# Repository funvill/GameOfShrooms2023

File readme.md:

Working on [Idea 006 Procedurally Generated Glowing Mushroom Pcb](https://blog.abluestar.com/idea006-procedurally-generated-glowing-mushroom-pcb/) Using [p5js](https://p5js.org/) to generate the mushroom and [svg2shenzhen](https://github.com/badgeek/svg2shenzhen) to convert the SVG to KiCad.

For [Game of Shroom 2023](https://yumfactory.com/gameofshrooms/)

## Build

1. Open `p5js/index.html` in a browser
2. Right click and inspect the image, find the svg, copy the element, past the svg text into a new text document, save it as `output.svg`
3. Install [svg2shenzhen](https://github.com/badgeek/svg2shenzhen)
4. Open `output.svg` in inkscape.
5. Extention->svg2shenzhen->`1. Prep Document...`
6. Resize the image to fit within the page.
7. Copy red outline to the `edge.cuts` layer
8. Copy the black body to the `f.Cu` layer
9. Extention->svg2shenzhen->`2. Export to KiCad`

## Example

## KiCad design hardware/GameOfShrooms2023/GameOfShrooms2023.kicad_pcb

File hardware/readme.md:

Based on this design
https://github.com/adafruit/Adafruit-QT-Py-ESP32-S2-PCB/tree/main

## BOM

- CPU (C529594) ESP32-S2 https://jlcpcb.com/partdetail/EspressifSystems-ESP32S2/C529594
- LED (C2843785) WS2812B XL-5050RGBC-WS2812B https://jlcpcb.com/partdetail/Xinglight-XL_5050RGBCWS2812B/C2843785
- Antenna (C89334) https://jlcpcb.com/partdetail/JohansonDielectrics-2450AT18A100E/C89334
- Linear Voltage Regulators (LDO) (C51118) https://jlcpcb.com/partdetail/DiodesIncorporated-AP2112K_33TRG1/C51118

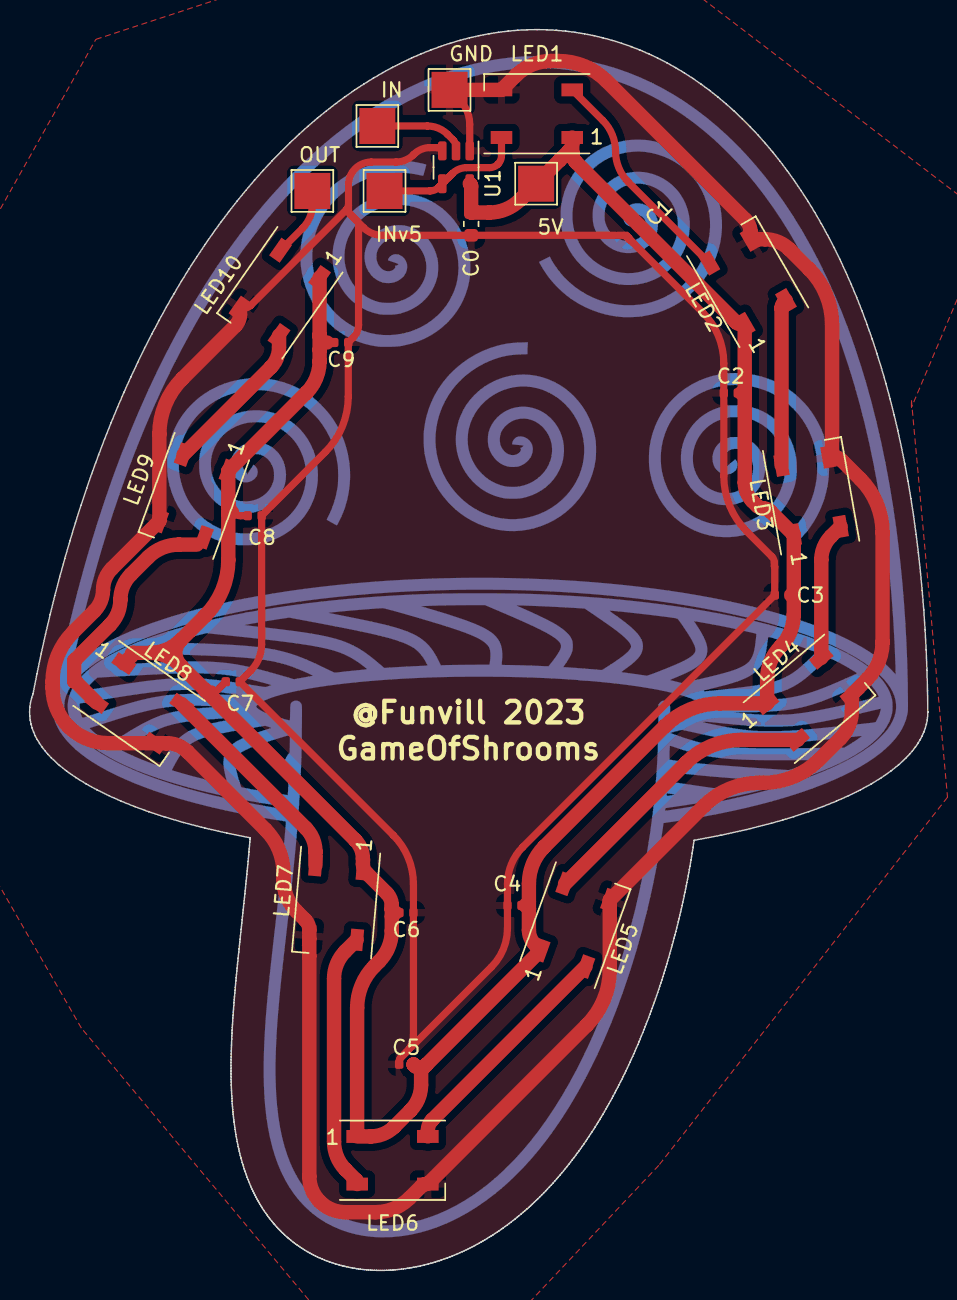
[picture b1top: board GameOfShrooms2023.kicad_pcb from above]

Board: 2 copper layers, 62.2 x 86.0 mm, 26 parts (0 on the bottom side), 14 nets.

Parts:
5V: TestPoint; TestPoint_Pad_2.5x2.5mm
C0: 10uF,10V,X5R; C_0603_1608Metric
C1, C2, C3, C4, C5, C6, C7, C8, C9: 1uF,25V,X5R; C_0402_1005Metric
GND: TestPoint; TestPoint_Pad_2.5x2.5mm
IN: TestPoint; TestPoint_Pad_2.5x2.5mm
INv5: TestPoint; TestPoint_Pad_2.5x2.5mm
LED1, LED2, LED3, LED4, LED5, LED6, LED7, LED8, LED9, LED10: WS2812B; LED_WS2812B_PLCC4_5.0x5.0mm_P3.2mm
OUT: TestPoint; TestPoint_Pad_2.5x2.5mm
U1: 74AHC1G125; SOT-23-5

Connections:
+5V: 5V.1, C0.1, C1.2, C2.2, C3.2, C4.2, C5.2, C6.2, C7.2, C8.2, C9.2, LED1.1 (VDD), LED2.1 (VDD), LED3.1 (VDD), LED4.1 (VDD), LED5.1 (VDD), LED6.1 (VDD), LED7.1 (VDD), LED8.1 (VDD), LED9.1 (VDD), LED10.1 (VDD), U1.5 (VCC)
GND: C0.2, C1.1, C2.1, C3.1, C4.1, C5.1, C6.1, C7.1, C8.1, C9.1, GND.1, LED1.3 (GND), LED2.3 (GND), LED3.3 (GND), LED4.3 (GND), LED5.3 (GND), LED6.3 (GND), LED7.3 (GND), LED8.3 (GND), LED9.3 (GND), LED10.3 (GND), U1.1, U1.3 (GND)
LED_IN: IN.1, U1.2
LED_OUT: LED10.2 (DOU), OUT.1
unnamed: INv5.1, LED1.4 (DIN), U1.4
unnamed: LED1.2 (DOU), LED2.4 (DIN)
unnamed: LED2.2 (DOU), LED3.4 (DIN)
unnamed: LED3.2 (DOU), LED4.4 (DIN)
unnamed: LED4.2 (DOU), LED5.4 (DIN)
unnamed: LED5.2 (DOU), LED6.4 (DIN)
unnamed: LED6.2 (DOU), LED7.4 (DIN)
unnamed: LED7.2 (DOU), LED8.4 (DIN)
unnamed: LED8.2 (DOU), LED9.4 (DIN)
unnamed: LED9.2 (DOU), LED10.4 (DIN)

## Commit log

2023-05-16 working toolchain
2023-05-16 Added instructions
2023-05-28 Added a random seed for all the mushroom settings
2023-05-28 Added p5.svg.js to directory instead of CDN
2023-05-29 Added bezier to stem
2023-05-29 Added settings panel
2023-05-31 Initial version of the PCB
2023-06-01 Exported Gerbers
